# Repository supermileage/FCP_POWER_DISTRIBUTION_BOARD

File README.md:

FINAL BOARD is on branch CHANGES. Not FINAL

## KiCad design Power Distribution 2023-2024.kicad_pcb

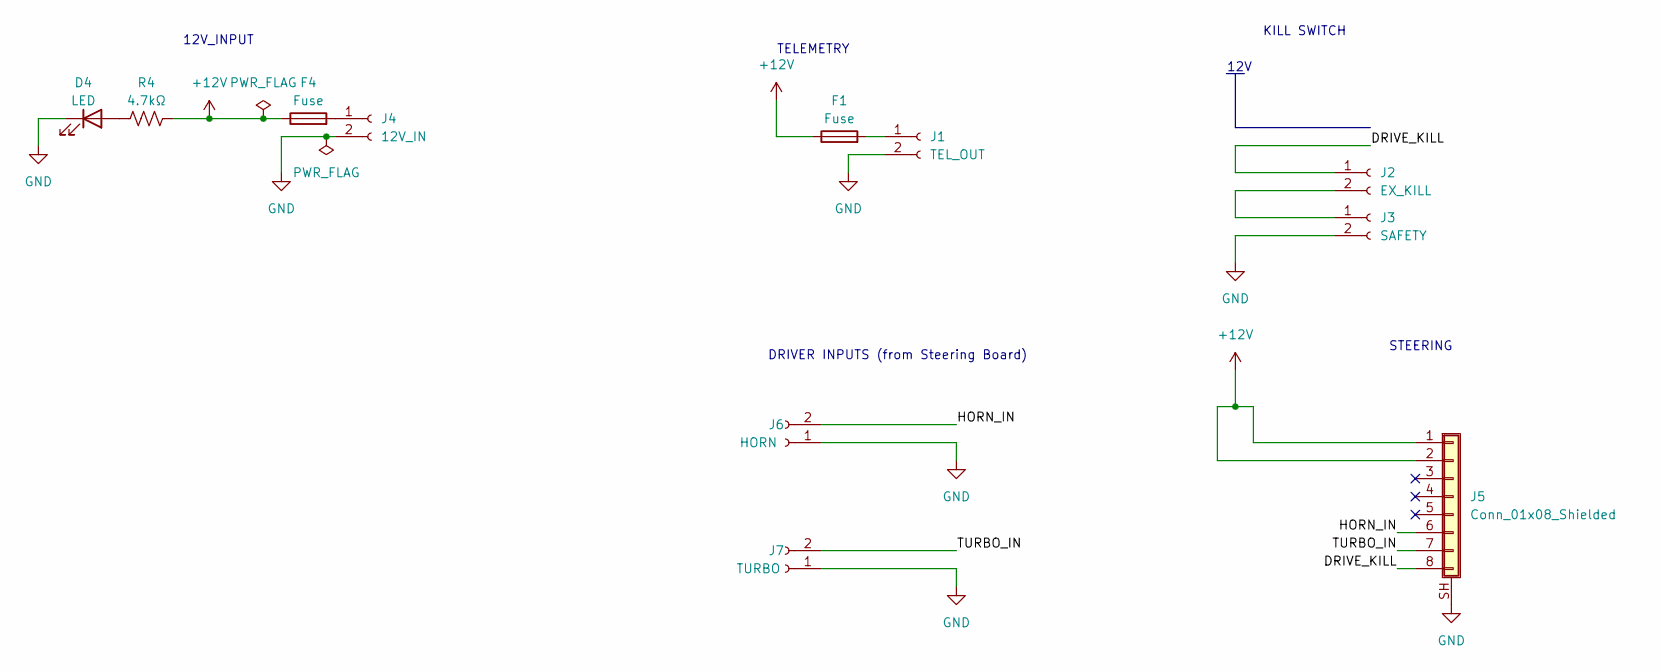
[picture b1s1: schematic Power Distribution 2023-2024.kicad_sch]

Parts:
D4: LED; LED_0805_2012Metric
F1, F4: Fuse; Fuseholder_Blade_Mini_Keystone_3568
J1: TEL_OUT; Molex_Micro-Fit_3.0_43650-0200_1x02_P3.00mm_Horizontal
J2: EX_KILL; Molex_Micro-Fit_3.0_43650-0200_1x02_P3.00mm_Horizontal
J3: SAFETY; Molex_Micro-Fit_3.0_43650-0200_1x02_P3.00mm_Horizontal
J4: 12V_IN; Molex_MegaFit_20024_1x02_P5.70mm_Horizontal
J5: Conn_01x08_Shielded; RJ45_Amphenol_RJHSE5380
J6: HORN; Molex_Mini-Fit_Jr_5569-02A2_2x01_P4.20mm_Horizontal
J7: TURBO; Molex_Mini-Fit_Jr_5569-02A2_2x01_P4.20mm_Horizontal
R4: 4.7kΩ; R_0805_2012Metric

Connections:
+12V: F1.1, F4.1, J5.1, J5.2, R4.2
/DRIVE_KILL: J2.1, J5.8
/HORN_IN: J5.6, J6.2
/TURBO_IN: J5.7, J7.2
GND: D4.1 (K), J1.2, J3.2, J4.2, J5.SH (Shield), J6.1, J7.1
unnamed: D4.2 (A), R4.1
unnamed: F1.2, J1.1
unnamed: J2.2, J3.1
unnamed: F4.2, J4.1

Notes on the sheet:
TELEMETRY
KILL SWITCH
12V
DRIVER INPUTS (from Steering Board)
STEERING
12V_INPUT

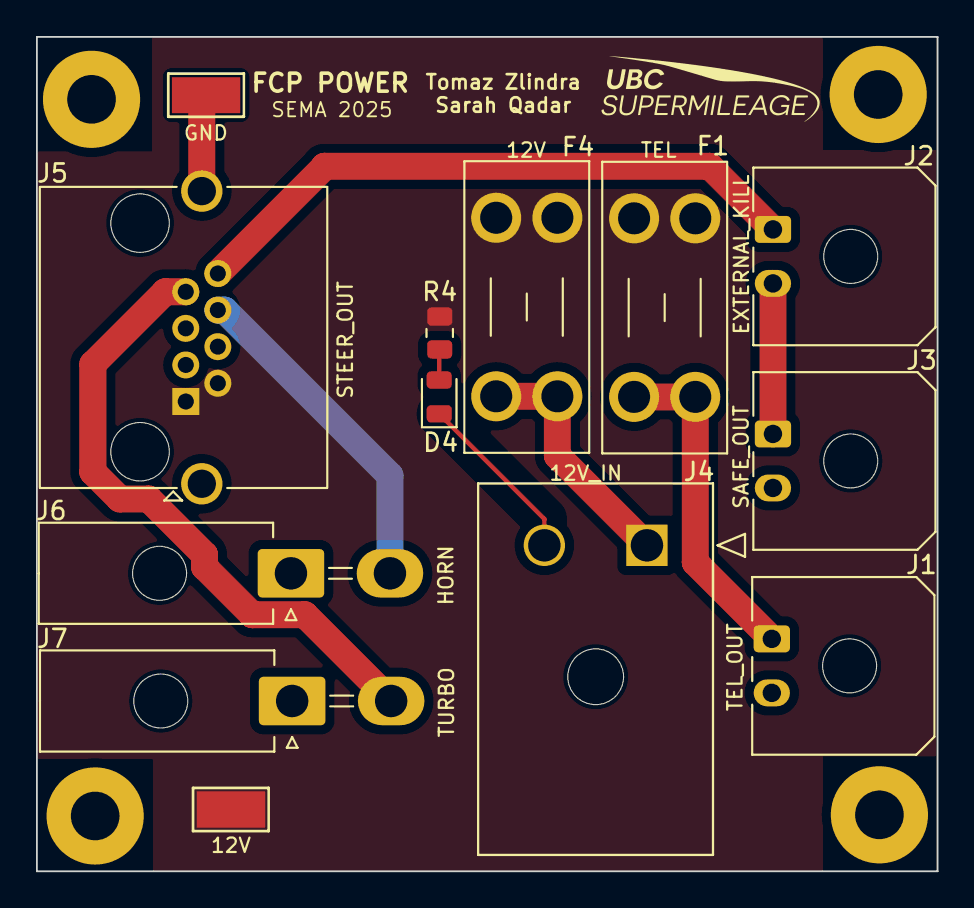
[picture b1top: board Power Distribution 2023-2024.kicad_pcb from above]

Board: 2 copper layers, 50.0 x 46.4 mm, 15 parts (0 on the bottom side), 9 nets.

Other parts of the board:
He1, He2, He3, He4: MountingHole; MountingHole_2.7mm_M2.5_Pad

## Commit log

2023-11-11 November 11th, 2023 12:41pm
2023-11-11 November 11th, 2nd commit
2023-11-18 PCB edits
2023-11-25 November 25th, 2023
2023-12-02 something
2023-12-02 December 2nd, 2023
2023-12-24 Small change
2023-12-24 small error
2024-01-13 cleaned up stuff
2024-01-13 FINAL for printing (unless there are any last changes)
2024-01-16 FINAL final final final
2024-01-18 Gerber
2024-01-27 Schematic
2024-02-10 DONE
2024-02-10 One last thing
2024-08-26 final touches
